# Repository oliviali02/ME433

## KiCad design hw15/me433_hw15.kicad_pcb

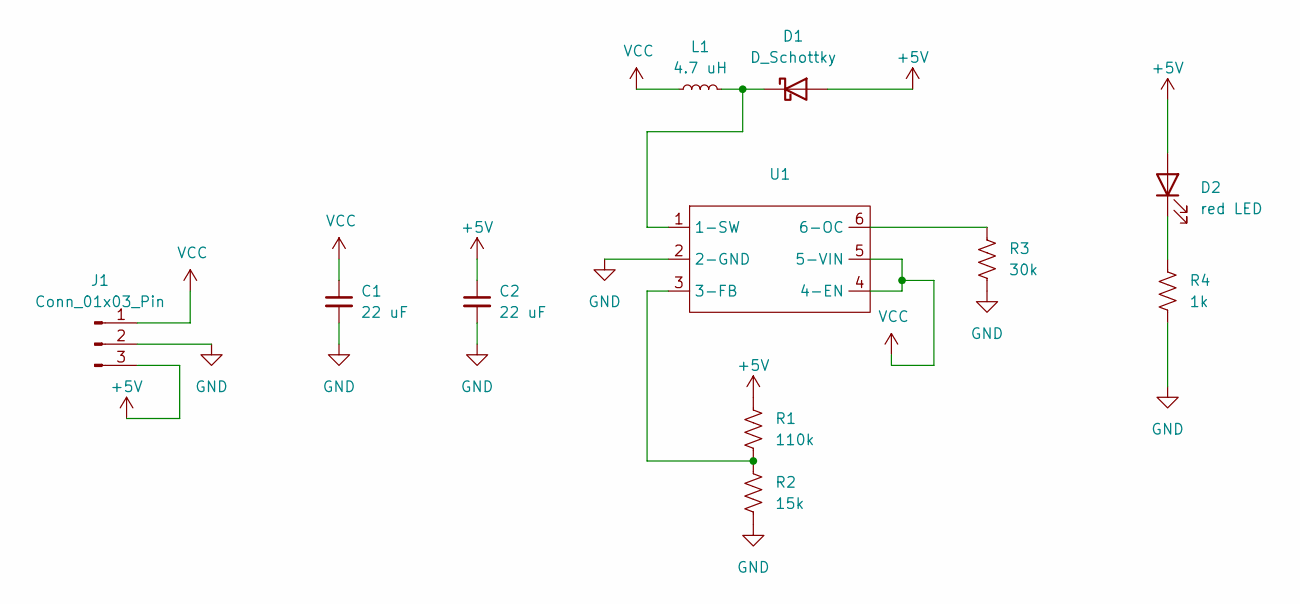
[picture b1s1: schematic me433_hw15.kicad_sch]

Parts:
C1, C2: 22 uF; C_1210_3225Metric
D1: D_Schottky; D_SOD-123
D2: red LED; LED_D3.0mm
J1: Conn_01x03_Pin; PinSocket_1x03_P2.54mm_Vertical
L1: 4.7 uH; L_0805_2012Metric
R1: 110k; R_0805_2012Metric
R2: 15k; R_0805_2012Metric
R3: 30k; R_0805_2012Metric
R4: 1k; R_0805_2012Metric
U1: SOT-23-6

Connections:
+5V: C2.1, D1.2 (A), D2.2 (A), J1.3, R1.1
GND: C1.2, C2.2, J1.2, R2.2, R3.2, R4.2, U1.2 (2-GND)
unnamed: D1.1 (K), L1.2, U1.1 (1-SW)
unnamed: D2.1 (K), R4.1
unnamed: R1.2, R2.1, U1.3 (3-FB)
unnamed: R3.1, U1.6 (6-OC)
VCC: C1.1, J1.1, L1.1, U1.4 (4-EN), U1.5 (5-VIN)

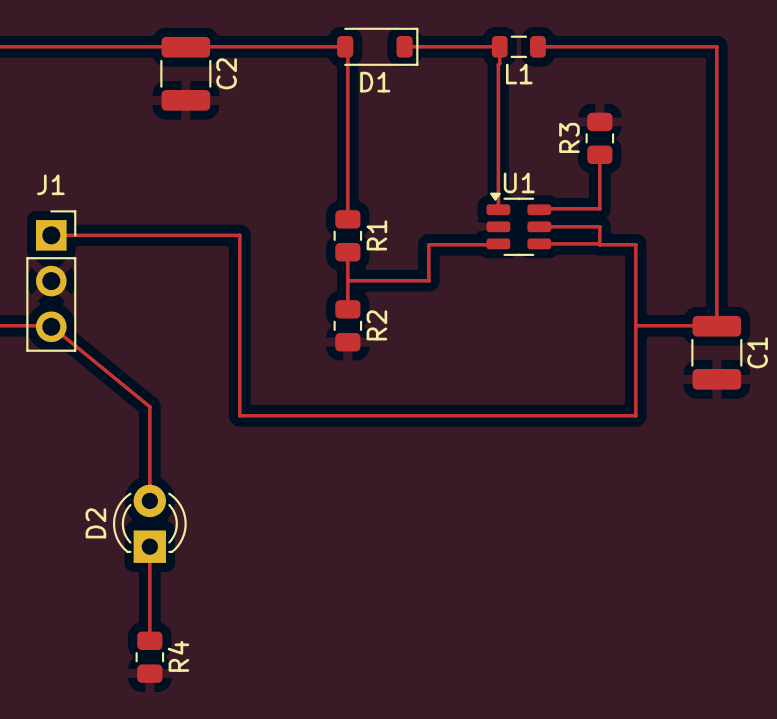
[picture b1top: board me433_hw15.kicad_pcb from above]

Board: 2 copper layers, 11 parts (0 on the bottom side), 7 nets.

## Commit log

2025-04-05 added blink example
2025-04-05 updated blink example
2025-04-05 added hello_usb example
2025-04-05 added hello_gpio_irq example
2025-04-06 changed blink delay to 1000 ms
2025-04-07 update hello_usb for assignment requirements
2025-04-08 created hw3 template
2025-04-08 created gitignore file
2025-04-08 tested external button and LED circuit
2025-04-08 added ability to read analog voltage
2025-04-08 removed .DS_Store
2025-04-08 completed assignment requirements
2025-04-08 updated formatting
2025-04-08 changed button pin number
2025-04-10 started homework 4
2025-04-14 implemented and tested writeDAC function
2025-04-14 included 2Hz sine wave
2025-04-14 added 1 Hz triangle wave
2025-04-14 added oscilloscope image
2025-04-15 added comments
2025-04-15 created hw5 and included pseudocode from lecture
2025-04-15 computed clock cycles for different floating point math operations
2025-04-15 added screenshot of floating point math cycles
2025-04-15 added screenshot of floating point math
2025-04-15 updated floating point math section to include input
2025-04-15 implemented ram_write function
2025-04-16 implemented and tested ram_read
2025-04-16 completed assignment and cleaned up code
2025-04-16 screenshot of 1 Hz sine wave
2025-04-16 Rename 2025-04-16_09-19-58.809.png to sine_wave.png
2025-04-17 created folder and implemented "heartbeat" LED
2025-04-18 completed initialization and writing with i2c
2025-04-18 completed assignment
2025-04-19 fixed timing of heartbeat
2025-04-22 creating hw7
2025-04-24 finishing up assignment
2025-04-24 deleting comments
2025-04-28 starting hw8
2025-04-28 finished assignment 8
2025-04-29 fixing timing of servo
2025-04-29 created hw9 from example code
2025-04-29 implemented LED and ADC initialization
2025-04-29 finished hw9
2025-04-29 cleaning up code
2025-04-29 added error message
2025-05-01 starting hw10
2025-05-05 implemented moving average filter and added plots
2025-05-05 fixing graphs for maf
2025-05-05 fixing graphs
2025-05-05 implemented and uploaded iir plots
2025-05-05 uploaded unfiltered data plots
2025-05-06 completed fir and uploaded plots
2025-05-06 created hw11 with sample code
2025-05-06 set up buttons
2025-05-06 implemented basic mouse movement
2025-05-06 fixed basic mouse movement
2025-05-06 having mouse adjust speed based on duration of press
2025-05-07 implemented mode button
2025-05-11 importing hw files
2025-05-11 commented out print statements
2025-05-13 starting hw13
2025-05-15 implemented printing of accel values
2025-05-21 added CAD files
2025-05-21 updating CAD files
2025-05-21 updating CAD files for proper wood thickness
2025-05-26 starting hw16
2025-05-26 debugging hw16
2025-05-26 finished hw16
2025-05-27 uploaded hw15 pcb
2025-05-27 uploaded images
